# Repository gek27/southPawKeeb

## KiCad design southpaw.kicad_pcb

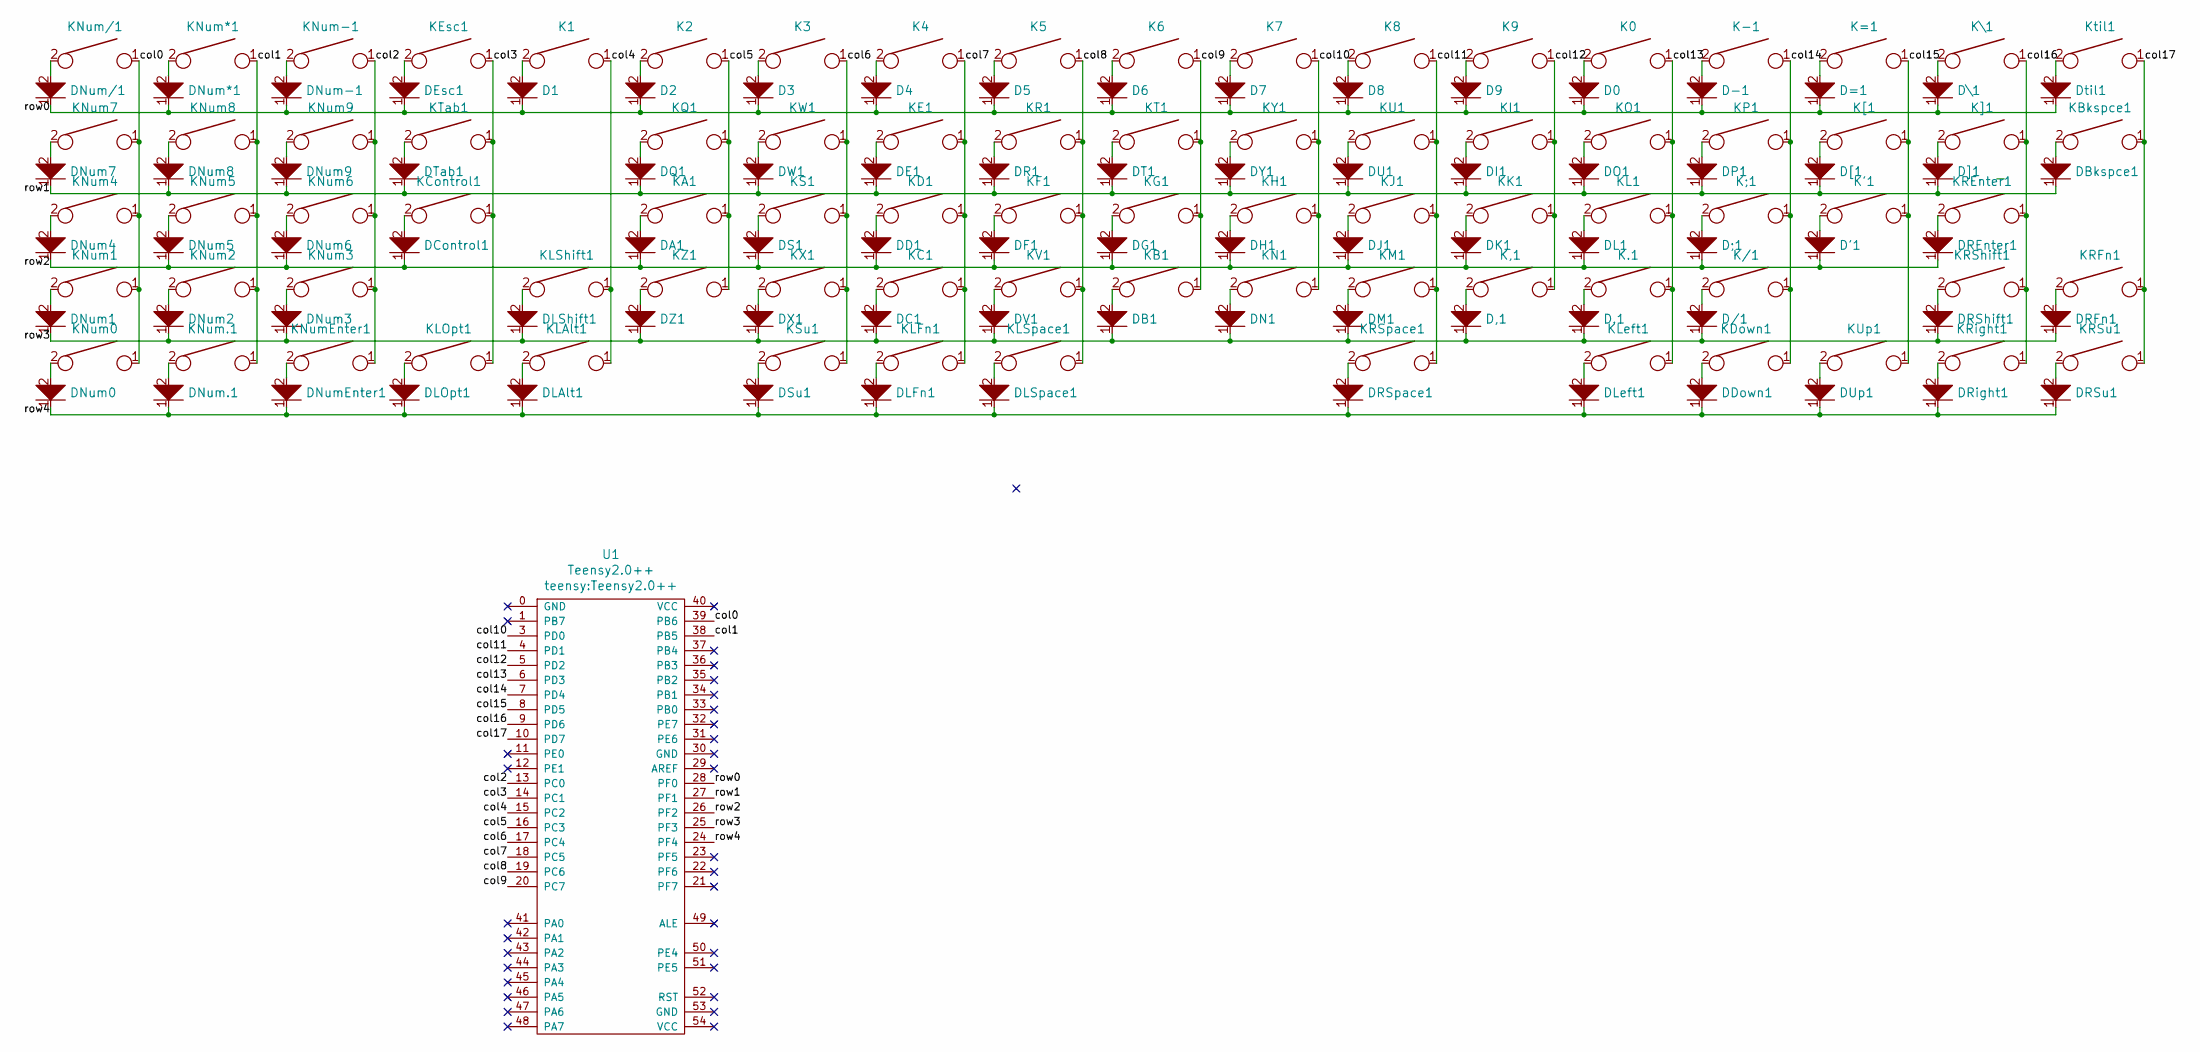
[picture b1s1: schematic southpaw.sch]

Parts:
D0, D1, D2, D3, D4, D5, D6, D7, D8, D9, D.1: D; D_SOD123_axial
D'1: D; D_SOD123_axial
D,1: D; D_SOD123_axial
D-1: D; D_SOD123_axial
D/1: D; D_SOD123_axial
D;1: D; D_SOD123_axial
D=1: D; D_SOD123_axial
DA1: D; D_SOD123_axial
DB1: D; D_SOD123_axial
DBkspce1: D; D_SOD123_axial
DC1: D; D_SOD123_axial
DControl1: D; D_SOD123_axial
DD1: D; D_SOD123_axial
DDown1: D; D_SOD123_axial
DE1: D; D_SOD123_axial
DEsc1: D; D_SOD123_axial
DF1: D; D_SOD123_axial
DG1: D; D_SOD123_axial
DH1: D; D_SOD123_axial
DI1: D; D_SOD123_axial
DJ1: D; D_SOD123_axial
DK1: D; D_SOD123_axial
DL1: D; D_SOD123_axial
DLAlt1: D; D_SOD123_axial
DLFn1: D; D_SOD123_axial
DLOpt1: D; D_SOD123_axial
DLShift1: D; D_SOD123_axial
DLSpace1: D; D_SOD123_axial
DLeft1: D; D_SOD123_axial
DM1: D; D_SOD123_axial
DN1: D; D_SOD123_axial
DNum0, DNum1, DNum2, DNum3, DNum4, DNum5, DNum6, DNum7, DNum8, DNum9, DNum.1: D; D_SOD123_axial
DNum*1: D; D_SOD123_axial
DNum-1: D; D_SOD123_axial
DNum/1: D; D_SOD123_axial
DNumEnter1: D; D_SOD123_axial
DO1: D; D_SOD123_axial
DP1: D; D_SOD123_axial
DQ1: D; D_SOD123_axial
DR1: D; D_SOD123_axial
DREnter1: D; D_SOD123_axial
DRFn1: D; D_SOD123_axial
DRShift1: D; D_SOD123_axial
DRSpace1: D; D_SOD123_axial
DRSu1: D; D_SOD123_axial
DRight1: D; D_SOD123_axial
DS1: D; D_SOD123_axial
DSu1: D; D_SOD123_axial
DT1: D; D_SOD123_axial
DTab1: D; D_SOD123_axial
DU1: D; D_SOD123_axial
DUp1: D; D_SOD123_axial
DV1: D; D_SOD123_axial
DW1: D; D_SOD123_axial
DX1: D; D_SOD123_axial
DY1: D; D_SOD123_axial
DZ1: D; D_SOD123_axial
D[1: D; D_SOD123_axial
D\1: D; D_SOD123_axial
D]1: D; D_SOD123_axial
Dtil1: D; D_SOD123_axial
K0, K1, K2, K3, K4, K5, K6, K7, K8, K9, K.1: KEYSW; Mx_Alps_100
K'1: KEYSW; Mx_Alps_100
K,1: KEYSW; Mx_Alps_100
K-1: KEYSW; Mx_Alps_100
K/1: KEYSW; Mx_Alps_100
K;1: KEYSW; Mx_Alps_100
K=1: KEYSW; Mx_Alps_100
KA1: KEYSW; Mx_Alps_100
KB1: KEYSW; Mx_Alps_100
KBkspce1: KEYSW; Mx_Alps_150
KC1: KEYSW; Mx_Alps_100
KControl1: KEYSW; Mx_Alps_175
KD1: KEYSW; Mx_Alps_100
KDown1: KEYSW; Mx_Alps_100
KE1: KEYSW; Mx_Alps_100
KEsc1: KEYSW; Mx_Alps_100
KF1: KEYSW; Mx_Alps_100
KG1: KEYSW; Mx_Alps_100
KH1: KEYSW; Mx_Alps_100
KI1: KEYSW; Mx_Alps_100
KJ1: KEYSW; Mx_Alps_100
KK1: KEYSW; Mx_Alps_100
KL1: KEYSW; Mx_Alps_100
KLAlt1: KEYSW; Mx_Alps_125
KLFn1: KEYSW; Mx_Alps_100
KLOpt1: KEYSW; Mx_Alps_125
KLShift1: KEYSW; Mx_Alps_225
KLSpace1: KEYSW; Mx_Alps_275
KLeft1: KEYSW; Mx_Alps_100
KM1: KEYSW; Mx_Alps_100
KN1: KEYSW; Mx_Alps_100
KNum0, KNum1, KNum2, KNum3, KNum4, KNum5, KNum6, KNum7, KNum8, KNum9, KNum.1: KEYSW; Mx_Alps_100
KNum*1: KEYSW; Mx_Alps_100
KNum-1: KEYSW; Mx_Alps_100
KNum/1: KEYSW; Mx_Alps_100
KNumEnter1: KEYSW; Mx_Alps_100
KO1: KEYSW; Mx_Alps_100
KP1: KEYSW; Mx_Alps_100
KQ1: KEYSW; Mx_Alps_100
KR1: KEYSW; Mx_Alps_100
KREnter1: KEYSW; Mx_Alps_225
KRFn1: KEYSW; Mx_Alps_100
KRShift1: KEYSW; Mx_Alps_175
KRSpace1: KEYSW; Mx_Alps_225
KRSu1: KEYSW; Mx_Alps_150
KRight1: KEYSW; Mx_Alps_100
KS1: KEYSW; Mx_Alps_100
KSu1: KEYSW; Mx_Alps_100
KT1: KEYSW; Mx_Alps_100
KTab1: KEYSW; Mx_Alps_150
KU1: KEYSW; Mx_Alps_100
KUp1: KEYSW; Mx_Alps_100
KV1: KEYSW; Mx_Alps_100
KW1: KEYSW; Mx_Alps_100
KX1: KEYSW; Mx_Alps_100
KY1: KEYSW; Mx_Alps_100
KZ1: KEYSW; Mx_Alps_100
K[1: KEYSW; Mx_Alps_100
K\1: KEYSW; Mx_Alps_100
K]1: KEYSW; Mx_Alps_100
Ktil1: KEYSW; Mx_Alps_100
U1: Teensy2.0++

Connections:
/col0: KNum0.1, KNum1.1, KNum4.1, KNum7.1, KNum/1.1, U1.39 (PB6)
/col1: KNum2.1, KNum5.1, KNum8.1, KNum*1.1, KNum.1.1, U1.38 (PB5)
/col2: KNum3.1, KNum6.1, KNum9.1, KNum-1.1, KNumEnter1.1, U1.13 (PC0)
/col3: KControl1.1, KEsc1.1, KLOpt1.1, KTab1.1, U1.14 (PC1)
/col4: K1.1, KLAlt1.1, KLShift1.1, U1.15 (PC2)
/col5: K2.1, KA1.1, KQ1.1, KZ1.1, U1.16 (PC3)
/col6: K3.1, KS1.1, KSu1.1, KW1.1, KX1.1, U1.17 (PC4)
/col7: K4.1, KC1.1, KD1.1, KE1.1, KLFn1.1, U1.18 (PC5)
/col8: K5.1, KF1.1, KLSpace1.1, KR1.1, KV1.1, U1.19 (PC6)
/col9: K6.1, KB1.1, KG1.1, KT1.1, U1.20 (PC7)
/col10: K7.1, KH1.1, KN1.1, KY1.1, U1.3 (PD0)
/col11: K8.1, KJ1.1, KM1.1, KRSpace1.1, KU1.1, U1.4 (PD1)
/col12: K9.1, K,1.1, KI1.1, KK1.1, U1.5 (PD2)
/col13: K0.1, K.1.1, KL1.1, KLeft1.1, KO1.1, U1.6 (PD3)
/col14: K-1.1, K/1.1, K;1.1, KDown1.1, KP1.1, U1.7 (PD4)
/col15: K'1.1, K=1.1, KUp1.1, K[1.1, U1.8 (PD5)
/col16: KREnter1.1, KRShift1.1, KRight1.1, K\1.1, K]1.1, U1.9 (PD6)
/col17: KBkspce1.1, KRFn1.1, KRSu1.1, Ktil1.1, U1.10 (PD7)
/row0: D0.1, D1.1, D2.1, D3.1, D4.1, D5.1, D6.1, D7.1, D8.1, D9.1, D-1.1, D=1.1, DEsc1.1, DNum*1.1, DNum-1.1, DNum/1.1, D\1.1, Dtil1.1, U1.28 (PF0)
/row1: DBkspce1.1, DE1.1, DI1.1, DNum7.1, DNum8.1, DNum9.1, DO1.1, DP1.1, DQ1.1, DR1.1, DT1.1, DTab1.1, DU1.1, DW1.1, DY1.1, D[1.1, D]1.1, U1.27 (PF1)
/row2: D'1.1, D;1.1, DA1.1, DControl1.1, DD1.1, DF1.1, DG1.1, DH1.1, DJ1.1, DK1.1, DL1.1, DNum4.1, DNum5.1, DNum6.1, DREnter1.1, DS1.1, U1.26 (PF2)
/row3: D,1.1, D.1.1, D/1.1, DB1.1, DC1.1, DLShift1.1, DM1.1, DN1.1, DNum1.1, DNum2.1, DNum3.1, DRFn1.1, DRShift1.1, DV1.1, DX1.1, DZ1.1, U1.25 (PF3)
/row4: DDown1.1, DLAlt1.1, DLFn1.1, DLOpt1.1, DLSpace1.1, DLeft1.1, DNum0.1, DNum.1.1, DNumEnter1.1, DRSpace1.1, DRSu1.1, DRight1.1, DSu1.1, DUp1.1, U1.24 (PF4)
unnamed: D0.2, K0.2
unnamed: D1.2, K1.2
unnamed: D2.2, K2.2
unnamed: D3.2, K3.2
unnamed: D4.2, K4.2
unnamed: D5.2, K5.2
unnamed: D6.2, K6.2
unnamed: D7.2, K7.2
unnamed: D8.2, K8.2
unnamed: D9.2, K9.2
unnamed: D'1.2, K'1.2
unnamed: D,1.2, K,1.2
unnamed: D-1.2, K-1.2
unnamed: D.1.2, K.1.2
unnamed: D/1.2, K/1.2
unnamed: D;1.2, K;1.2
unnamed: D=1.2, K=1.2
unnamed: DA1.2, KA1.2
unnamed: DB1.2, KB1.2
unnamed: DBkspce1.2, KBkspce1.2
unnamed: DC1.2, KC1.2
unnamed: DControl1.2, KControl1.2
unnamed: DD1.2, KD1.2
unnamed: DDown1.2, KDown1.2
unnamed: DE1.2, KE1.2
unnamed: DEsc1.2, KEsc1.2
unnamed: DF1.2, KF1.2
unnamed: DG1.2, KG1.2
unnamed: DH1.2, KH1.2
unnamed: DI1.2, KI1.2
unnamed: DJ1.2, KJ1.2
unnamed: DK1.2, KK1.2
unnamed: DL1.2, KL1.2
unnamed: DLAlt1.2, KLAlt1.2
unnamed: DLFn1.2, KLFn1.2
unnamed: DLOpt1.2, KLOpt1.2
unnamed: DLShift1.2, KLShift1.2
unnamed: DLSpace1.2, KLSpace1.2
unnamed: DLeft1.2, KLeft1.2
unnamed: DM1.2, KM1.2
unnamed: DN1.2, KN1.2
unnamed: DNum0.2, KNum0.2
unnamed: DNum1.2, KNum1.2
unnamed: DNum2.2, KNum2.2
unnamed: DNum3.2, KNum3.2
unnamed: DNum4.2, KNum4.2
unnamed: DNum5.2, KNum5.2
unnamed: DNum6.2, KNum6.2
unnamed: DNum7.2, KNum7.2
unnamed: DNum8.2, KNum8.2
unnamed: DNum9.2, KNum9.2
unnamed: DNum*1.2, KNum*1.2
unnamed: DNum-1.2, KNum-1.2
unnamed: DNum.1.2, KNum.1.2
unnamed: DNum/1.2, KNum/1.2
unnamed: DNumEnter1.2, KNumEnter1.2
unnamed: DO1.2, KO1.2
unnamed: DP1.2, KP1.2
unnamed: DQ1.2, KQ1.2
unnamed: DR1.2, KR1.2
unnamed: DREnter1.2, KREnter1.2
unnamed: DRFn1.2, KRFn1.2
unnamed: DRShift1.2, KRShift1.2
unnamed: DRSpace1.2, KRSpace1.2
unnamed: DRSu1.2, KRSu1.2
unnamed: DRight1.2, KRight1.2
unnamed: DS1.2, KS1.2
unnamed: DSu1.2, KSu1.2
unnamed: DT1.2, KT1.2
unnamed: DTab1.2, KTab1.2
unnamed: DU1.2, KU1.2
unnamed: DUp1.2, KUp1.2
unnamed: DV1.2, KV1.2
unnamed: DW1.2, KW1.2
unnamed: DX1.2, KX1.2
unnamed: DY1.2, KY1.2
unnamed: DZ1.2, KZ1.2
unnamed: D[1.2, K[1.2
unnamed: D\1.2, K\1.2
unnamed: D]1.2, K]1.2
unnamed: Dtil1.2, Ktil1.2

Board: 2 copper layers, 163 parts (1 on the bottom side), 104 nets, no tracks yet.

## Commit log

2020-12-18 Base Commit from Southpaw project
